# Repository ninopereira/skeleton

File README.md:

# Haunted Skeleton

Arduino sketch for an animatronic Halloween skeleton built on an
Arduino Uno.

- Plays the songs on the SD card in a random order, different on every
  power-up. No song repeats until all of them have played; then a new
  order is drawn.
- When a visitor walks up, the song pauses and one of the voice clips,
  picked at random but never the same twice in a row, plays with the jaw
  synced to it, and each arm goes up and back down, one slightly after
  the other. The song then resumes where it left off.
- The jaw then rests for at least 5 s before it can be triggered again.

## Hardware

| Part | Connection |
|---|---|
| VL53L0X time-of-flight sensor | **VIN on 3V3, not 5V**; GND → GND, SDA → A4, SCL → A5 |
| *or* HC-SR04 sonar | trig pin 7, echo pin 6 |
| DFPlayer Mini | **VCC on 3V3, not 5V**; module TX → pin 0 (RX); pin 1 (TX) → 680 Ω → module RX, 1 kΩ from module RX to GND; module BUSY → A0 |
| Jaw servo | pin 9 |
| Arm servos | left: pin 10, right: pin 11 |
| Eye LEDs | pin 8 |

All pins, angles, distances and timings live in [`config.hpp`](config.hpp).
Set `DISTANCE_SENSOR` there to the sensor you fitted:
`DistanceSensorType::TIME_OF_FLIGHT` (VL53L0X) or
`DistanceSensorType::SONAR` (HC-SR04). The detection range
(`DETECT_MIN_CM` / `DETECT_MAX_CM`) applies to both.

The VL53L0X runs on 3.3 V and its SDA/SCL pins are not 5 V tolerant. The
sketch turns off the Uno's internal pull-ups (which go to 5 V), so the
sensor board's own pull-ups to 3.3 V must hold the lines high; if the
board has none, fit 4.7 kΩ from SDA and from SCL to 3V3. The bus runs at
100 kHz because 3.3 V only just counts as high for the Uno. Peel off the
protective film over the lens.

The 3V3 pin also feeds the DFPlayer and can only supply about 150 mA
(Uno R3). If the sensor drops out while music plays loudly, power both
from a separate 3.3 V regulator instead.

With the VL53L0X in place of the sonar:

## Setup

1. Install the **Servo**, **DFRobotDFPlayerMini** (1.0.6) and
   **VL53L0X** by Pololu (1.3.1) libraries in the Arduino IDE. The
   VL53L0X library is needed even when the sonar is selected.
2. Format a FAT32 SD card and copy the songs to its root (they play
   shuffled, so their order does not matter, but copy them before the
   voice clips: the module numbers tracks by copy order). Then create a
   folder `ADVERT` and copy the voice clips from `sd_card/` into it,
   renamed so each starts with a **4-digit** number:
   `0001_WhoAreYou.mp3`, `0002_ComeHere.mp3`, ... (the module only reads
   the first four digits). An advert pauses the song and the song resumes
   where it left off. Set `MP3_SONG_COUNT` in `config.hpp` to the number
   of songs.
   After adding, removing or changing a voice clip, regenerate the jaw
   scripts with `python3 tools/make_jaw_script.py` (needs numpy and
   ffmpeg); clip N in `sd_card/` must be advert N on the card.
3. Power the servos well: three servos (two lifting arms) can draw more
   current than the board's 5 V regulator supplies.
4. If the eyes blink 5 times at power-up, the MP3 player or its SD card
   did not answer: check the wiring and the card. `tools/mp3_test` tests
   the player on its own. If they blink 3 times, the VL53L0X did not
   answer: check its I2C wiring. `tools/tof_test` tests the sensor on
   its own.
5. Calibrate `MOUTH_CLOSED_DEG` / `MOUTH_OPEN_DEG` and the arm angles and
   sweep times in `config.hpp` for your build.

## Hardware serial

The DFPlayer is on the Uno's only hardware serial port (pins 0/1). A
software serial port would block interrupts for about 1 ms per byte,
which stretches the servo pulses and makes the arms jerk past their
limits. As a result:

- The Serial Monitor cannot be used by the sketch; anything printed
  would go to the DFPlayer. Faults are reported by the eye blinks.
  `tools/tof_test` still prints to the Serial Monitor; `tools/mp3_test`
  shows its results on the eye LEDs instead.
- The USB port shares pins 0/1. If an upload fails, disconnect the
  module's TX from pin 0 while uploading.

## Code layout

| File | Purpose |
|---|---|
| `skeleton.ino` | Entry point |
| `haunted_skeleton.*` | Behaviour state machine |
| `mp3_player.*` | DFPlayer Mini wrapper |
| `presence_sensor.hpp` | Picks the sensor selected in `config.hpp` |
| `presence_filter.*` | Debounced presence detection shared by both sensors |
| `tof_sensor.*` | VL53L0X time-of-flight sensor |
| `sonar.*` | HC-SR04 ultrasonic sensor |
| `mouth.*` | Scripted jaw animation |
| `arm.*`, `arms.*` | Staggered up-and-down servo arm gesture |
| `eyes.*` | Eye LEDs |

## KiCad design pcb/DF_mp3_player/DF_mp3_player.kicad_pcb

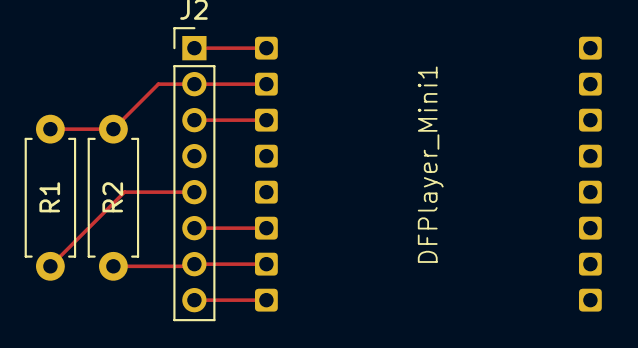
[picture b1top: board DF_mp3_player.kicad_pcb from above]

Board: 2 copper layers, 4 parts (0 on the bottom side), 7 nets.

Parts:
DFPlayer_Mini1: DFPlayer_Mini
J2: Conn_01x08_Pin; PinHeader_1x08_P2.00mm_Vertical
R1: 680; R_Axial_DIN0207_L6.3mm_D2.5mm_P7.62mm_Horizontal
R2: 1K; R_Axial_DIN0207_L6.3mm_D2.5mm_P7.62mm_Horizontal

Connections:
GND: DFPlayer_Mini1.7 (GND), J2.7, R2.2
unnamed: DFPlayer_Mini1.2 (RX), J2.2, R1.2, R2.1
unnamed: DFPlayer_Mini1.6 (SPK1), J2.6
unnamed: DFPlayer_Mini1.8 (SPK2), J2.8
unnamed: DFPlayer_Mini1.3 (TX), J2.3
unnamed: J2.5, R1.1
VCC: DFPlayer_Mini1.1 (VCC), J2.1
